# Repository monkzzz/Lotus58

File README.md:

### Notice! Project files in the development branches are NOT intended for public use in production of PCB's, may or may not be tested and may change or be removed without notice! 
If you order PCB's from these, YOU have the sole responsibility for how these turn out!!! 

**Please use the Gerber files for producing PCB's, found under the header 'Releases' instead (Look here >>).** 

Also please note the difference between a 'Pre-release' (partially/fully untested, basically what I order a prototype PCB from to test) and a full actual 'Release' which is fully tested, built and ready to be used to produce PCB's.

# Lotus 58 Glow - Classic
#### Lotus 58 Classic is the wired designs of the Lotus keyboard. Wireless with BLE and 2.4Ghz dongled wireless reside in other repositories.

Starting with simple tweaks to the Lily58 Glow before ordering a set of PCB's it quickly spiraled out of control, and I ended up with what wasn't quite a Lily58 anymore, and although very similar in layout, it is no longer compatible with plate and case design. 

Because of this, it was renamed Lotus58, referencing another flower much like the lily in the name Lily58.

(photo from reddit by u/bduzik)

## General Specifications

- Layout very similar to the original Lily58 family
- Per key RGB and RGB underglow
- Kaihl Hot-swap sockets for MX compatible switches
- Can be used as a standalone Gamepad for either hand
- Optional 0.91" OLED Screens and rotary encoders (one each per side)
- All components through-hole and easily soldered for beginners (SMD option for diodes)
- Designed with a sandwich-style plate/case as part of the design

## Layout variations

- Optional plate layout with OLED screen (Encoder can be placed on upper thumb key position)
- Optional plate layout with rotary encoder (Removes OLED screen for that side)  
- Optional plate layout with no hole for OLED or upper encoder (Encoder can be placed on upper thumb key position)

## 3D-printed Cases
**There are a couple of 'official' commissioned designs for 3D printed cases for the Lotus 58 Glow, available in a separate Git [here](https://github.com/TweetyDaBird/Lotus-Cases).** 

And you can find several more made by users using Google, and/or by joining the Discord channel and chatting to the builders/designers and users.

## Things to note when ordering PCB's
### Finding the Gerber files
If you are not aiming at modifying things, don't look for the gerber files in the folders, pretty please!</BR>
And please don't open yet another issue about it! </BR>
The gerber files are where they belong, zipped up in releases, look under that header for the version you want.

### Tips & Tricks
- Most PCB manufacturers have a MOQ of 5 PCB's, meaning you end up with 2½ keyboards when finished.
- The recommended PCB thickness is 1.6 mm, both for the main PCB and plates to allow the keyswitches to grip the plate and lock in place securely.

If ordering from [JLCPCB](https://www.jlcpcb.com) the plate Gerber files include a reference putting the added serial etc on a breakaway part for a clean look with minimal cost, if using another manufacturer it's possible they have additional fee's for removing the extra text, or you should consider plotting the Gerber files yourself with the correct reference for your manufacturer. Otherwise use the standard settings from JLPCB.

## Build guide
**Some basic build instructions are in the [WIKI](https://github.com/TweetyDaBird/Lotus-58-Classic/wiki), and I really try to keep these updated.** But please keep in mind that whenever these instructions conflict with information on the PCB silkscreen, the silkscreen is and always will be the correct source of information! It's always updated with the version, and the most current information for the PCB version in question. 

**The intent has always been that the keyboard should be able to be fully built with some very basic soldering skills and the instructions on the silkscreen.**

### Discord for further build help and discussions!

## Buy a kit!
I sell complete kits, making it easy to build your keyboard, and it also supports prototypes for new wacky ones.

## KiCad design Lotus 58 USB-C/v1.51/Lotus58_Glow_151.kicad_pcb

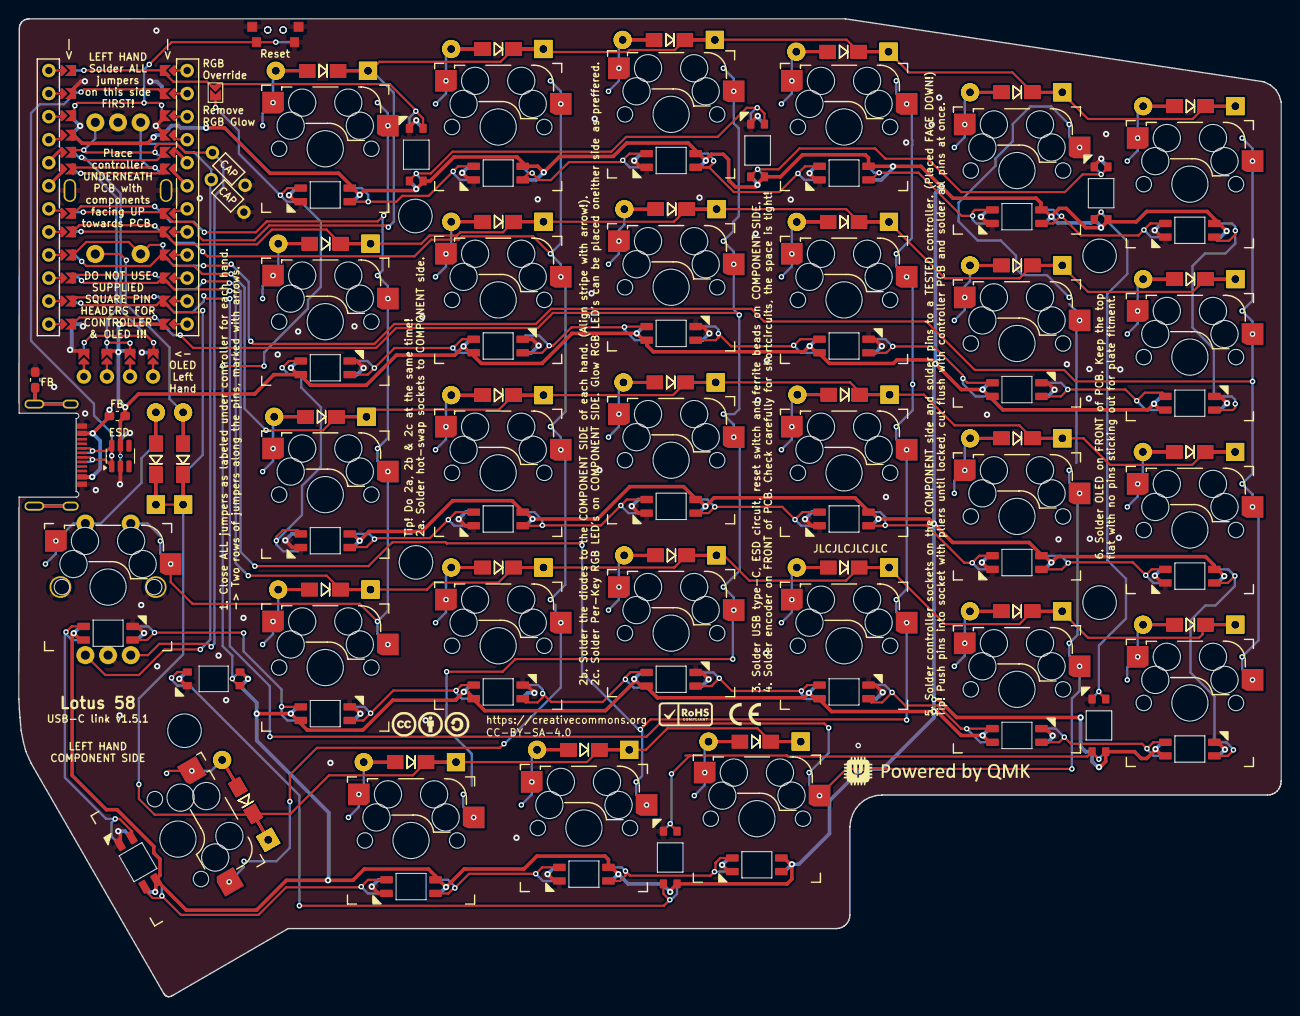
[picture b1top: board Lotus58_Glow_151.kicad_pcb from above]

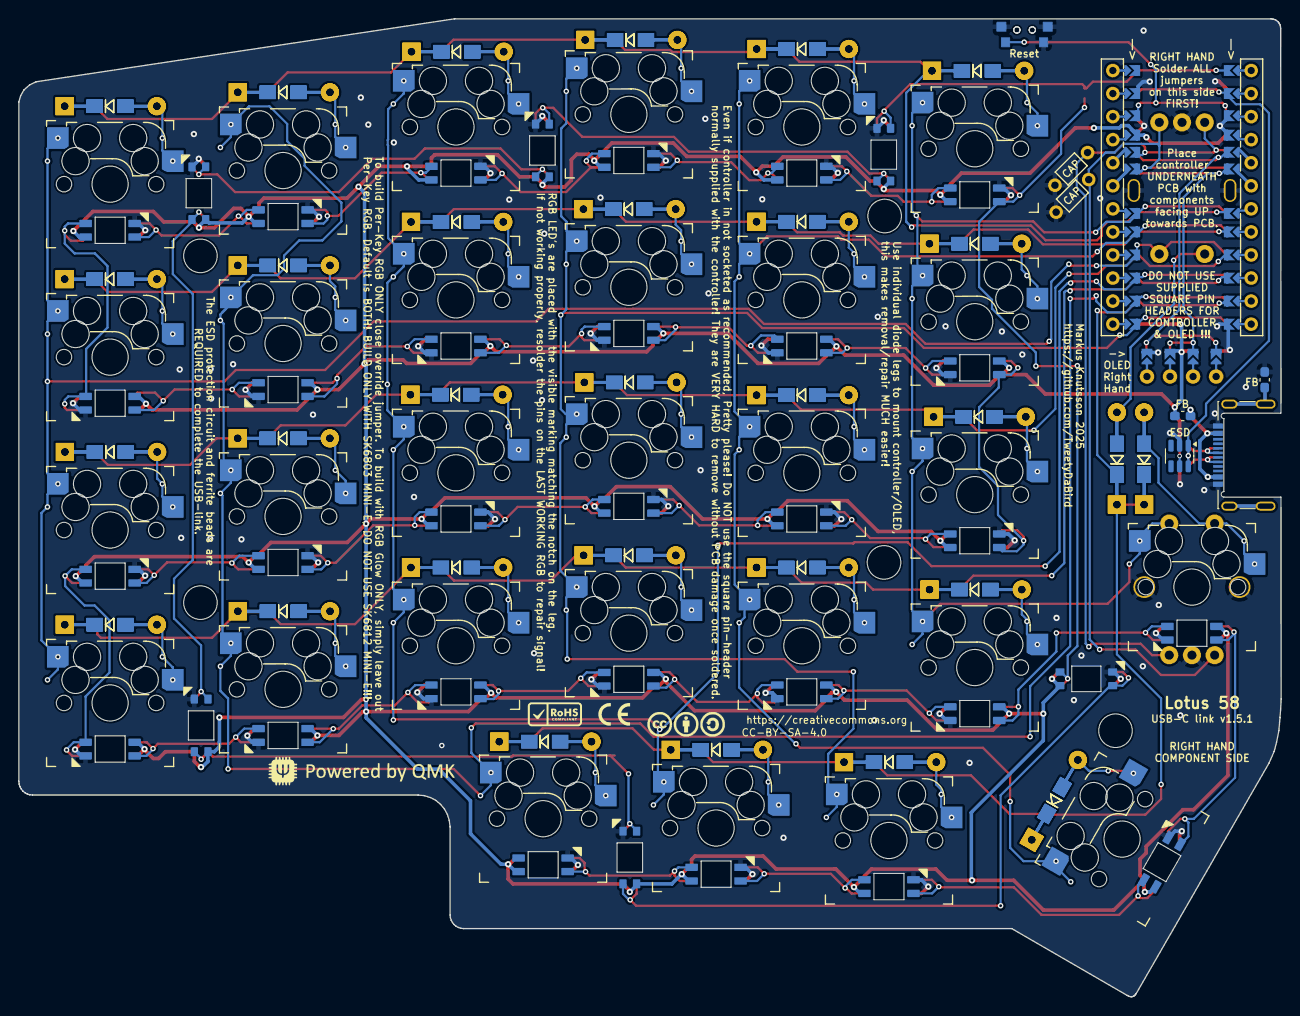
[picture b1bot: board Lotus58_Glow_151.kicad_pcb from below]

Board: 2 copper layers, 139.1 x 107.7 mm, 151 parts (40 on the bottom side), 86 nets.

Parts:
C1, C2: 50V/100nF axial; RESISTOR_Reversible
D1, D2, D3, D4, D5, D6, D7, D8, D9, D10, D11, D12, D13, D14, D15, D16, D17, D18, D19, D20, D21, D22, D23, D24, D25, D26, D27, D28, D29, D30, D31, D32, D33, D34, D35, D36, D37, D38, D39, D40, D41, D42, D43, D44, D45, D46, D47, D48, D49, D50, D51, D52, D53, D54, D55, D56, D57, D58, D59, D60: 1N4148/1N4148W; Diode_DO35_SOD123
ENC30: EC11; Encoder_Alps_EC11E_Small
ENC31: EC11; Encoder_Alps_EC11E_Small_onkey
FB1, FB2, FB3, FB4: 0603/150-200R; C_0603_1608Metric_Pad1.08x0.95mm_HandSolder
J1: HRO-TYPE-C-31-M-13x; Molex-216990_GCT-USB45xx_HRO-TYPE-C-31-M-13x-PiMicro_1_DOUB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
JP1: LEFT; Jumper_min_v2
LED1, LED2, LED3, LED4, LED5, LED6, LED7, LED8, LED9, LED10, LED11, LED12, LED13, LED14, LED15, LED16, LED17, LED18, LED19, LED20, LED21, LED22, LED23, LED24, LED25, LED26, LED27, LED28, LED29: SK6803MINI-E; MX_SK6812MINI-E_REVERSIBLE
LED30, LED31, LED32, LED33, LED34, LED35: SK6803MINI-E; MX_SK6812MINI-E_REVERSIBLE_special_v2
Logo1, Logo2: QMK_Logo; qmk logo
Logo4, Logo6: CE_Logo; CE
Logo7, Logo8: CC-BY-SA-4.0; CC_BY_SA_40_line
P1: OLED; SSD1306-0.91-OLED-4pin-128x32 doublesided
RES1, RES2: TS-A002; YTS-A002
SW1, SW2, SW3, SW4, SW5, SW6, SW7, SW8, SW9, SW10, SW11, SW12, SW13, SW14, SW15, SW16, SW17, SW18, SW19, SW20, SW21, SW22, SW23, SW24, SW25, SW26, SW27, SW28, SW29: Kailh hotswap MX socket; SW_MX_HotSwap_Reversible
TH1, TH2, TH3, TH4, TH5: HOLE; Spacer PCB hole
U1: Controller; ProMicro_jumpers_V3
U2, U3: SRV05-4; SOT-23-6

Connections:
/VCC_LINK: FB1.1, FB4.1, J1.A4 (VBUS), J1.A9 (VBUS), J1.B4 (VBUS), J1.B9 (VBUS)
Alt: D25.2 (A), D51.2 (A), ENC31.S2, SW25.1
DATA: J1.A7 (D-), J1.B7 (D-), U1.2 (RX1/PD2), U2.1 (IO1), U2.6 (IO4), U3.1 (IO1), U3.6 (IO4)
EncA: C2.2, ENC30.A, ENC31.A, U1.19 (A2/PF5)
EncB: C1.2, ENC30.B, ENC31.B, U1.20 (A3/PF4)
GND: C1.1, C2.1, ENC30.C, ENC30.MP (GND), ENC31.C, ENC31.MP (GND), FB2.2, FB3.2, J1.A1 (GND), J1.A12 (GND), J1.B1 (GND), J1.B12 (GND), LED1.3 (GND), LED2.3 (GND), LED3.3 (GND), LED4.3 (GND), LED5.3 (GND), LED6.3 (GND), LED7.3 (GND), LED8.3 (GND), LED9.3 (GND), LED10.3 (GND), LED11.3 (GND), LED12.3 (GND), LED13.3 (GND), LED14.3 (GND), LED15.3 (GND), LED16.3 (GND), LED17.3 (GND), LED18.3 (GND), LED19.3 (GND), LED20.3 (GND), LED21.3 (GND), LED22.3 (GND), LED23.3 (GND), LED24.3 (GND), LED25.3 (GND), LED26.3 (GND), LED27.3 (GND), LED28.3 (GND), LED29.3 (GND), LED30.3 (GND), LED31.3 (GND), LED32.3 (GND), LED33.3 (GND), LED34.3 (GND), LED35.3 (GND), P1.1 (GND), RES1.2, RES1.3, RES2.2, RES2.3, U1.3 (GND), U1.4 (GND), U1.12B, U1.23 (GND), U2.2 (VN), U3.2 (VN)
KEY: JP1.1 (A), LED1.4 (DIN), LED35.2 (DOUT)
LED: JP1.2 (B), LED30.4 (DIN), U1.1 (TX0/PD3)
unnamed: D1.2 (A), D31.2 (A), SW1.1
unnamed: D2.2 (A), D32.2 (A), SW2.1
unnamed: D3.2 (A), D33.2 (A), SW3.1
unnamed: D10.2 (A), D40.2 (A), SW10.1
unnamed: D11.2 (A), D41.2 (A), SW11.1
unnamed: D12.2 (A), D42.2 (A), SW12.1
unnamed: D13.2 (A), D48.2 (A), SW13.1
unnamed: D14.2 (A), D47.2 (A), SW14.1
unnamed: D15.2 (A), D46.2 (A), SW15.1
unnamed: D16.2 (A), D45.2 (A), SW16.1
unnamed: D17.2 (A), D44.2 (A), SW17.1
unnamed: D18.2 (A), D43.2 (A), SW18.1
unnamed: D19.2 (A), D49.2 (A), SW19.1
unnamed: D20.2 (A), D50.2 (A), SW20.1
unnamed: D21.2 (A), D56.2 (A), SW21.1
unnamed: D22.2 (A), D57.2 (A), SW22.1
unnamed: D23.2 (A), D58.2 (A), SW23.1
unnamed: D24.2 (A), D59.2 (A), SW24.1
unnamed: D26.2 (A), D52.2 (A), SW26.1
unnamed: D27.2 (A), D53.2 (A), SW27.1
unnamed: D28.2 (A), D54.2 (A), SW28.1
unnamed: D29.2 (A), D55.2 (A), SW29.1
unnamed: D30.2 (A), D60.2 (A), ENC30.S1
unnamed: D4.2 (A), D34.2 (A), SW4.1
unnamed: D5.2 (A), D35.2 (A), SW5.1
unnamed: D6.2 (A), D36.2 (A), SW6.1
unnamed: D7.2 (A), D37.2 (A), SW7.1
unnamed: D8.2 (A), D38.2 (A), SW8.1
unnamed: D9.2 (A), D39.2 (A), SW9.1
unnamed: FB2.1, FB3.1, J1.S1 (SHIELD)
unnamed: LED1.2 (DOUT), LED2.4 (DIN)
unnamed: LED2.2 (DOUT), LED3.4 (DIN)
unnamed: LED3.2 (DOUT), LED4.4 (DIN)
unnamed: LED4.2 (DOUT), LED5.4 (DIN)
unnamed: LED5.2 (DOUT), LED6.4 (DIN)
unnamed: LED7.4 (DIN), LED8.2 (DOUT)
unnamed: LED8.4 (DIN), LED9.2 (DOUT)
unnamed: LED10.4 (DIN), LED11.2 (DOUT)
unnamed: LED9.4 (DIN), LED10.2 (DOUT)
unnamed: LED11.4 (DIN), LED12.2 (DOUT)
unnamed: LED6.2 (DOUT), LED12.4 (DIN)
unnamed: LED7.2 (DOUT), LED13.4 (DIN)
unnamed: LED13.2 (DOUT), LED14.4 (DIN)
unnamed: LED14.2 (DOUT), LED15.4 (DIN)
unnamed: LED15.2 (DOUT), LED16.4 (DIN)
unnamed: LED16.2 (DOUT), LED17.4 (DIN)
unnamed: LED17.2 (DOUT), LED18.4 (DIN)
unnamed: LED18.2 (DOUT), LED24.4 (DIN)
unnamed: LED19.4 (DIN), LED20.2 (DOUT)
unnamed: LED19.2 (DOUT), LED25.4 (DIN)
unnamed: LED20.4 (DIN), LED21.2 (DOUT)
unnamed: LED21.4 (DIN), LED22.2 (DOUT)
unnamed: LED22.4 (DIN), LED23.2 (DOUT)
unnamed: LED23.4 (DIN), LED24.2 (DOUT)
unnamed: LED25.2 (DOUT), LED26.4 (DIN)
unnamed: LED26.2 (DOUT), LED27.4 (DIN)
unnamed: LED27.2 (DOUT), LED28.4 (DIN)
unnamed: LED28.2 (DOUT), LED29.4 (DIN)
unnamed: LED30.2 (DOUT), LED31.4 (DIN)
unnamed: LED31.2 (DOUT), LED32.4 (DIN)
unnamed: LED32.2 (DOUT), LED33.4 (DIN)
unnamed: LED33.2 (DOUT), LED34.4 (DIN)
unnamed: LED34.2 (DOUT), LED35.4 (DIN)
RESET: RES1.1, RES2.1, U1.22 (RST)
SCL: P1.3 (SCL), U1.6 (3/PD0)
SDA: P1.4 (SDA), U1.5 (2/PD1)
VCC: FB1.2, FB4.2, LED1.1 (VDD), LED2.1 (VDD), LED3.1 (VDD), LED4.1 (VDD), LED5.1 (VDD), LED6.1 (VDD), LED7.1 (VDD), LED8.1 (VDD), LED9.1 (VDD), LED10.1 (VDD), LED11.1 (VDD), LED12.1 (VDD), LED13.1 (VDD), LED14.1 (VDD), LED15.1 (VDD), LED16.1 (VDD), LED17.1 (VDD), LED18.1 (VDD), LED19.1 (VDD), LED20.1 (VDD), LED21.1 (VDD), LED22.1 (VDD), LED23.1 (VDD), LED24.1 (VDD), LED25.1 (VDD), LED26.1 (VDD), LED27.1 (VDD), LED28.1 (VDD), LED29.1 (VDD), LED30.1 (VDD), LED31.1 (VDD), LED32.1 (VDD), LED33.1 (VDD), LED34.1 (VDD), LED35.1 (VDD), P1.2 (VCC), U1.12A (9/PB5), U1.21 (VCC), U2.5 (VP), U3.5 (VP)
col0: ENC30.S2, SW6.2, SW12.2, SW18.2, SW24.2, U1.16 (15/PB1)
col1: SW5.2, SW11.2, SW17.2, SW23.2, SW29.2, U1.14 (16/PB2)
col2: SW4.2, SW10.2, SW16.2, SW22.2, SW28.2, U1.15 (14/PB3)
col3: SW3.2, SW9.2, SW15.2, SW21.2, SW27.2, U1.13 (10/PB6)
col4: SW2.2, SW8.2, SW14.2, SW20.2, SW26.2, U1.17 (A0/PF7)
col5: ENC31.S1, SW1.2, SW7.2, SW13.2, SW19.2, SW25.2, U1.18 (A1/PF6)
row0: D1.1 (K), D2.1 (K), D3.1 (K), D4.1 (K), D5.1 (K), D6.1 (K), D31.1 (K), D32.1 (K), D33.1 (K), D34.1 (K), D35.1 (K), D36.1 (K), U1.7 (4/PD4)
row1: D7.1 (K), D8.1 (K), D9.1 (K), D10.1 (K), D11.1 (K), D12.1 (K), D37.1 (K), D38.1 (K), D39.1 (K), D40.1 (K), D41.1 (K), D42.1 (K), U1.8 (5/PC6)
row2: D13.1 (K), D14.1 (K), D15.1 (K), D16.1 (K), D17.1 (K), D18.1 (K), D43.1 (K), D44.1 (K), D45.1 (K), D46.1 (K), D47.1 (K), D48.1 (K), U1.9 (6/PD7)
row3: D19.1 (K), D20.1 (K), D21.1 (K), D22.1 (K), D23.1 (K), D24.1 (K), D49.1 (K), D50.1 (K), D56.1 (K), D57.1 (K), D58.1 (K), D59.1 (K), U1.10 (7/PE6)
row4: D25.1 (K), D26.1 (K), D27.1 (K), D28.1 (K), D29.1 (K), D30.1 (K), D51.1 (K), D52.1 (K), D53.1 (K), D54.1 (K), D55.1 (K), D60.1 (K), U1.11 (8/PB4)

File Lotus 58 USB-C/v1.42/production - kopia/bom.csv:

Designator,Footprint,Quantity,Value,LCSC Part #
"D1, D10, D11, D12, D13, D14, D15, D16, D17, D18, D19, D2, D20, D21, D22, D23, D24, D25, D26, D27, D28, D29, D3, D30, D4, D5, D6, D7, D8, D9",Diode_DO35_SOD123,60,1N4148/1N4148W,C7420318
"FB1, FB2",603,4,Ferrite Bead,C882974
USB,Molex-216990_GCT-USB45xx_HRO-TYPE-C-31-M-13x-PiMicro_1_DOUBLESIDED,1,USB_C_Receptacle_USB2.0,C963373
"LED1, LED10, LED11, LED12, LED13, LED14, LED15, LED16, LED17, LED18, LED19, LED2, LED20, LED21, LED22, LED23, LED24, LED25, LED26, LED27, LED28, LED29, LED3, LED30, LED31, LED32, LED33, LED34, LED35, LED4, LED5, LED6, LED7, LED8, LED9",MX_SK6812MINI-E_REVERSIBLE,29,SK6803MINI-E,C5242955
RES,YTS-A002,2,TS-A002,C2888934
"SW1, SW10, SW11, SW12, SW13, SW14, SW15, SW16, SW17, SW18, SW19, SW2, SW20, SW21, SW22, SW23, SW24, SW25, SW26, SW27, SW28, SW29, SW3, SW4, SW5, SW6, SW7, SW8, SW9",SW_MX_HotSwap_Reversible,28,Kailh hotswap MX socket,C5156480
SEL,MSK12C02,2,MSK12C02,C431540
ESD,SOT-23-6,2,SRV05-4,C558418

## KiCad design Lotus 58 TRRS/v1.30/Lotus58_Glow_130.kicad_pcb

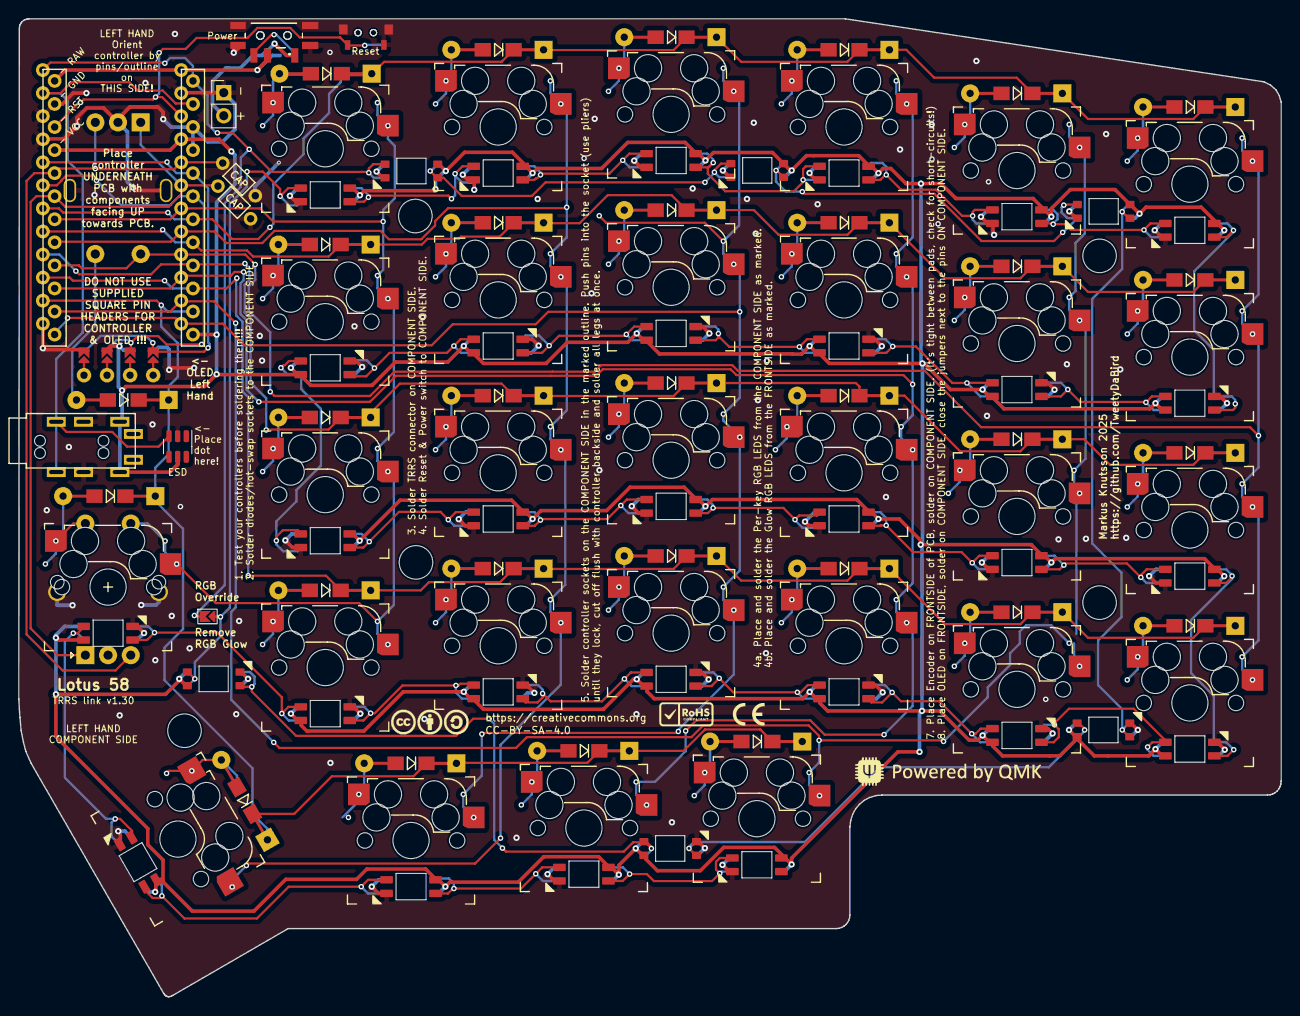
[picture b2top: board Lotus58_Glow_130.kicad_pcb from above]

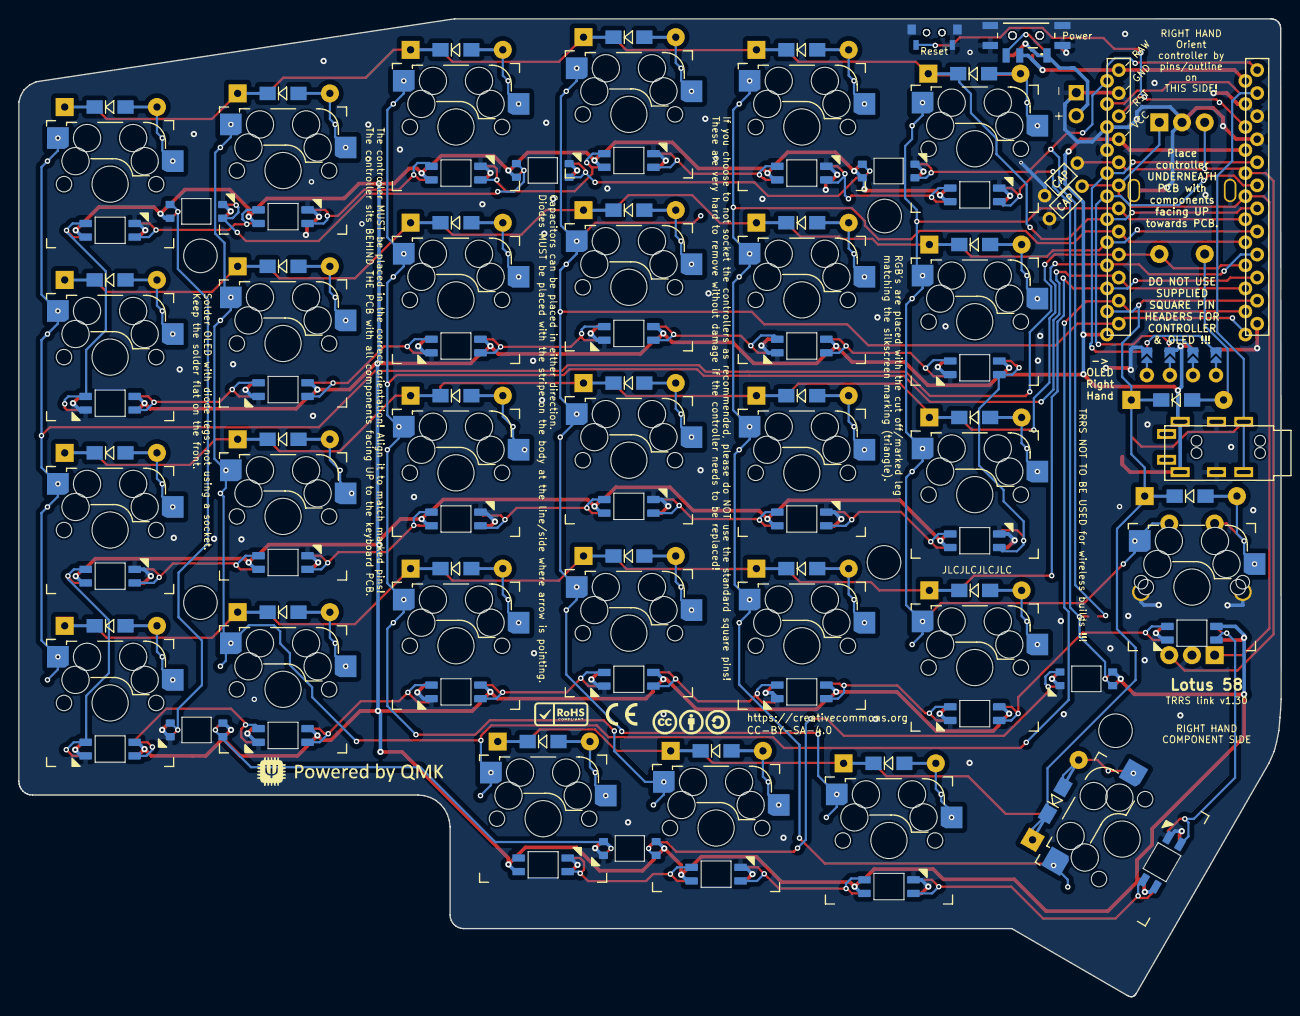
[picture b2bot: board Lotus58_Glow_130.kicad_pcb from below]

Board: 2 copper layers, 139.1 x 107.7 mm, 119 parts (71 on the bottom side), 86 nets.

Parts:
C1, C2: 50V/100nF axial; RESISTOR_Reversible
D1, D2, D3, D4, D5, D6, D7, D8, D9, D10, D11, D12, D13, D14, D15, D16, D17, D18, D19, D20, D21, D22, D23, D24, D25, D26, D27, D28, D29, D30: 1N4148/1N4148W; Diode_DO35_SOD123
J1: PJ-320A; MJ-4PP-9_alim
J2: Conn_01x02; PinHeader_1x02_P2.54mm_Vertical
JP5: FULL; Jumper_min_v2
LED1, LED2, LED3, LED4, LED5, LED6: SK6812MINI-E; MX_SK6812MINI-E_REVERSIBLE_special_v2
LED7, LED8, LED9, LED10, LED11, LED12, LED13, LED14, LED15, LED16, LED17, LED18, LED19, LED20, LED21, LED22, LED23, LED24, LED25, LED26, LED27, LED28, LED29, LED30, LED31, LED32, LED33, LED34, LED35: SK6803MINI-E; MX_SK6812MINI-E_REVERSIBLE
Logo1, Logo8: QMK_Logo; qmk logo
Logo2, Logo7: CC-BY-SA-4.0; CC_BY_SA_40_line
Logo5, Logo6: CE_Logo; CE
P1: OLED; SSD1306-0.91-OLED-4pin-128x32 doublesided
RES1, RES2: TS-A002; YTS-A002
S1, S2: MSK12C02
SW1, SW2, SW3, SW4, SW5, SW6, SW7, SW8, SW9, SW10, SW11, SW12, SW13, SW14, SW15, SW16, SW17, SW18, SW19, SW20, SW21, SW22, SW23, SW24, SW25, SW26, SW27, SW28, SW29: Kailh hotswap MX socket; SW_MX_HotSwap_Reversible
SW30: EC_11; RotaryEncoder_Alps_EC11E-Switch_Vertical_H20_special
SW31: EC_11; RotaryEncoder_Alps_EC11E-Switch_Special
TH1, TH2, TH3, TH4, TH5: HOLE; Spacer PCB hole
U1: Controller; ProMicro_Reversible_orig
U2: SRV05-4; SOT-23-6

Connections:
/Batt: J2.2, S1.NC, S2.NC
A: C2.2, SW30.A, SW31.A, U1.19 (A2/PF5)
Alt: D25.2 (A), SW25.2, SW31.S2
B: C1.2, SW30.B, SW31.B, U1.20 (A3/PF4)
Battery: S1.COM, S2.COM, U1.24 (RAW)
DATA: J1.R2, U1.2 (RX1/PD2), U2.3 (IO2)
GND: C1.1, C2.1, J1.R1, J2.1, LED1.3 (GND), LED2.3 (GND), LED3.3 (GND), LED4.3 (GND), LED5.3 (GND), LED6.3 (GND), LED7.3 (GND), LED8.3 (GND), LED9.3 (GND), LED10.3 (GND), LED11.3 (GND), LED12.3 (GND), LED13.3 (GND), LED14.3 (GND), LED15.3 (GND), LED16.3 (GND), LED17.3 (GND), LED18.3 (GND), LED19.3 (GND), LED20.3 (GND), LED21.3 (GND), LED22.3 (GND), LED23.3 (GND), LED24.3 (GND), LED25.3 (GND), LED26.3 (GND), LED27.3 (GND), LED28.3 (GND), LED29.3 (GND), LED30.3 (GND), LED31.3 (GND), LED32.3 (GND), LED33.3 (GND), LED34.3 (GND), LED35.3 (GND), P1.1 (GND), RES1.2, RES1.3, RES2.2, RES2.3, S1.MP (GND), S2.MP (GND), SW30.C, SW30.MP1 (GND), SW30.MP2 (GND), SW31.C, SW31.MP1 (GND), SW31.MP2 (GND), U1.3 (GND), U1.4 (GND), U1.23 (GND), U2.2 (VN)
LED: JP5.1, LED1.4 (DIN), U1.1 (TX0/PD3)
unnamed: D1.2 (A), SW1.2
unnamed: D2.2 (A), SW2.2
unnamed: D3.2 (A), SW3.2
unnamed: D4.2 (A), SW4.2
unnamed: D5.2 (A), SW5.2
unnamed: D6.2 (A), SW6.2
unnamed: D7.2 (A), SW7.2
unnamed: D8.2 (A), SW8.2
unnamed: D9.2 (A), SW9.2
unnamed: D10.2 (A), SW10.2
unnamed: D11.2 (A), SW11.2
unnamed: D12.2 (A), SW12.2
unnamed: D13.2 (A), SW13.2
unnamed: D14.2 (A), SW14.2
unnamed: D15.2 (A), SW15.2
unnamed: D16.2 (A), SW16.2
unnamed: D17.2 (A), SW17.2
unnamed: D18.2 (A), SW18.2
unnamed: D19.2 (A), SW19.2
unnamed: D20.2 (A), SW20.2
unnamed: D21.2 (A), SW21.2
unnamed: D22.2 (A), SW22.2
unnamed: D23.2 (A), SW23.2
unnamed: D24.2 (A), SW24.2
unnamed: D26.2 (A), SW26.2
unnamed: D27.2 (A), SW27.2
unnamed: D28.2 (A), SW28.2
unnamed: D29.2 (A), SW29.2
unnamed: D30.2 (A), SW30.S1
unnamed: LED1.2 (DOUT), LED2.4 (DIN)
unnamed: LED2.2 (DOUT), LED3.4 (DIN)
unnamed: LED3.2 (DOUT), LED4.4 (DIN)
unnamed: LED4.2 (DOUT), LED5.4 (DIN)
unnamed: LED5.2 (DOUT), LED6.4 (DIN)
unnamed: LED7.2 (DOUT), LED8.4 (DIN)
unnamed: LED8.2 (DOUT), LED9.4 (DIN)
unnamed: LED9.2 (DOUT), LED10.4 (DIN)
unnamed: LED10.2 (DOUT), LED11.4 (DIN)
unnamed: LED11.2 (DOUT), LED12.4 (DIN)
unnamed: LED12.2 (DOUT), LED18.4 (DIN)
unnamed: LED13.4 (DIN), LED14.2 (DOUT)
unnamed: LED13.2 (DOUT), LED19.4 (DIN)
unnamed: LED14.4 (DIN), LED15.2 (DOUT)
unnamed: LED15.4 (DIN), LED16.2 (DOUT)
unnamed: LED16.4 (DIN), LED17.2 (DOUT)
unnamed: LED17.4 (DIN), LED18.2 (DOUT)
unnamed: LED19.2 (DOUT), LED20.4 (DIN)
unnamed: LED20.2 (DOUT), LED21.4 (DIN)
unnamed: LED21.2 (DOUT), LED22.4 (DIN)
unnamed: LED22.2 (DOUT), LED23.4 (DIN)
unnamed: LED23.2 (DOUT), LED24.4 (DIN)
unnamed: LED24.2 (DOUT), LED30.4 (DIN)
unnamed: LED25.4 (DIN), LED26.2 (DOUT)
unnamed: LED25.2 (DOUT), LED31.4 (DIN)
unnamed: LED26.4 (DIN), LED27.2 (DOUT)
unnamed: LED27.4 (DIN), LED28.2 (DOUT)
unnamed: LED28.4 (DIN), LED29.2 (DOUT)
unnamed: LED29.4 (DIN), LED30.2 (DOUT)
unnamed: LED31.2 (DOUT), LED32.4 (DIN)
unnamed: LED32.2 (DOUT), LED33.4 (DIN)
unnamed: LED33.2 (DOUT), LED34.4 (DIN)
unnamed: LED34.2 (DOUT), LED35.4 (DIN)
RESET: RES1.1, RES2.1, U1.22 (RST)
RGB_LINK: JP5.2, LED6.2 (DOUT), LED7.4 (DIN)
SCL: P1.3 (SCL), U1.6 (3/PD0)
SDA: P1.4 (SDA), U1.5 (2/PD1)
VCC: J1.T, LED1.1 (VCC), LED2.1 (VCC), LED3.1 (VCC), LED4.1 (VCC), LED5.1 (VCC), LED6.1 (VCC), LED7.1 (VCC), LED8.1 (VCC), LED9.1 (VCC), LED10.1 (VCC), LED11.1 (VCC), LED12.1 (VCC), LED13.1 (VCC), LED14.1 (VCC), LED15.1 (VCC), LED16.1 (VCC), LED17.1 (VCC), LED18.1 (VCC), LED19.1 (VCC), LED20.1 (VCC), LED21.1 (VCC), LED22.1 (VCC), LED23.1 (VCC), LED24.1 (VCC), LED25.1 (VCC), LED26.1 (VCC), LED27.1 (VCC), LED28.1 (VCC), LED29.1 (VCC), LED30.1 (VCC), LED31.1 (VCC), LED32.1 (VCC), LED33.1 (VCC), LED34.1 (VCC), LED35.1 (VCC), P1.2 (VCC), U1.21 (VCC), U2.5 (VP)
col0: SW6.1, SW12.1, SW18.1, SW24.1, SW30.S2, U1.16 (15/PB1)
col1: SW5.1, SW11.1, SW17.1, SW23.1, SW29.1, U1.14 (16/PB2)
col2: SW4.1, SW10.1, SW16.1, SW22.1, SW28.1, U1.15 (14/PB3)
col3: SW3.1, SW9.1, SW15.1, SW21.1, SW27.1, U1.13 (10/PB6)
col4: SW2.1, SW8.1, SW14.1, SW20.1, SW26.1, U1.17 (A0/PF7)
col5: SW1.1, SW7.1, SW13.1, SW19.1, SW25.1, SW31.S1, U1.18 (A1/PF6)
row0: D1.1 (K), D2.1 (K), D3.1 (K), D4.1 (K), D5.1 (K), D6.1 (K), U1.7 (4/PD4)
row1: D7.1 (K), D8.1 (K), D9.1 (K), D10.1 (K), D11.1 (K), D12.1 (K), U1.8 (5/PC6)
row2: D13.1 (K), D14.1 (K), D15.1 (K), D16.1 (K), D17.1 (K), D18.1 (K), U1.9 (6/PD7)
row3: D19.1 (K), D20.1 (K), D21.1 (K), D22.1 (K), D23.1 (K), D24.1 (K), U1.10 (7/PE6)
row4: D25.1 (K), D26.1 (K), D27.1 (K), D28.1 (K), D29.1 (K), D30.1 (K), U1.11 (8/PB4)

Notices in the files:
Lotus 58 EZ/v1.00/Lotus58_EZ_100.kicad_pcb:
Licensed under Creative Commons BY-SA 4.0 International
Lotus 58 USB-C/v1.51/Lotus58_Glow_151.kicad_pcb:
Licensed under CERN-OHL-S v2 or any superseding version
